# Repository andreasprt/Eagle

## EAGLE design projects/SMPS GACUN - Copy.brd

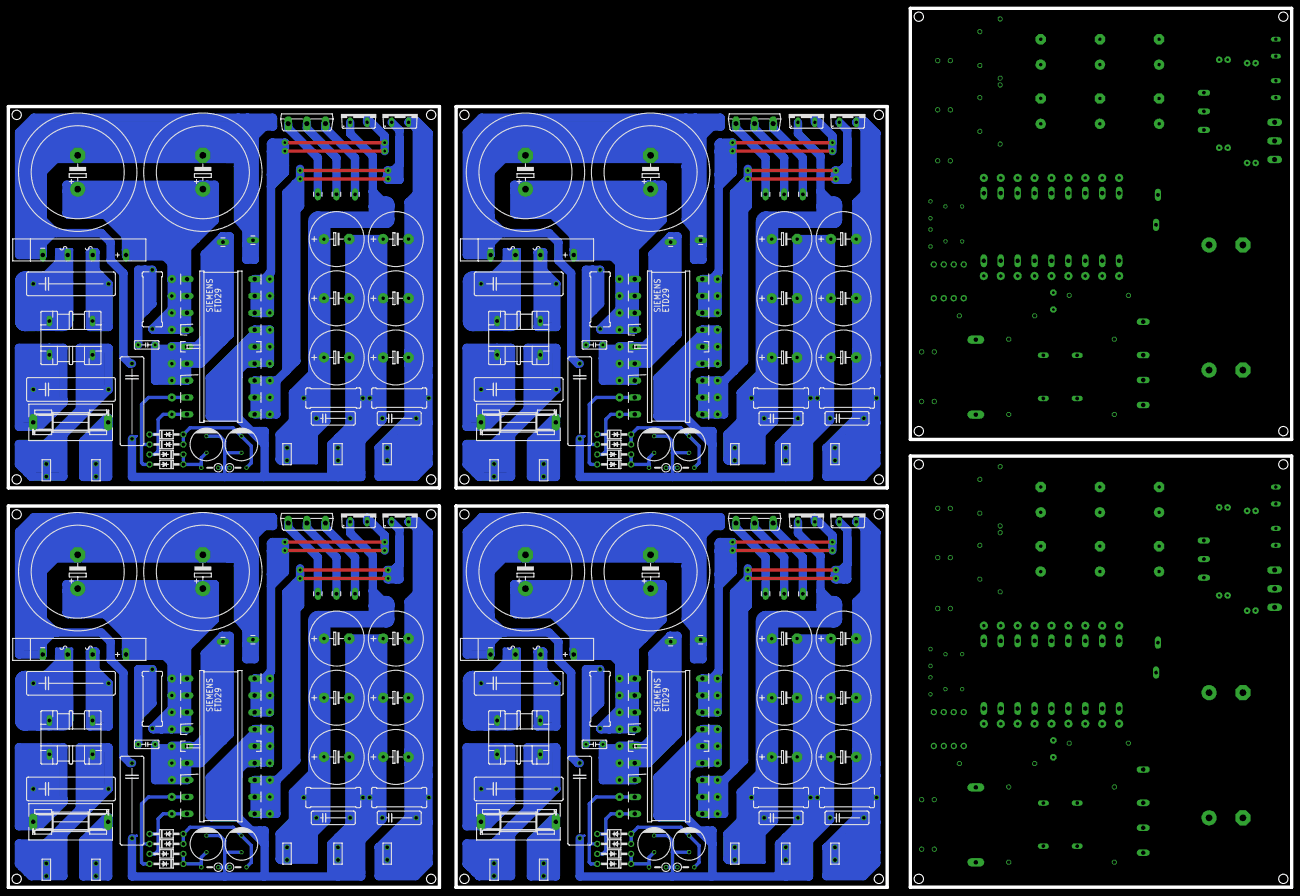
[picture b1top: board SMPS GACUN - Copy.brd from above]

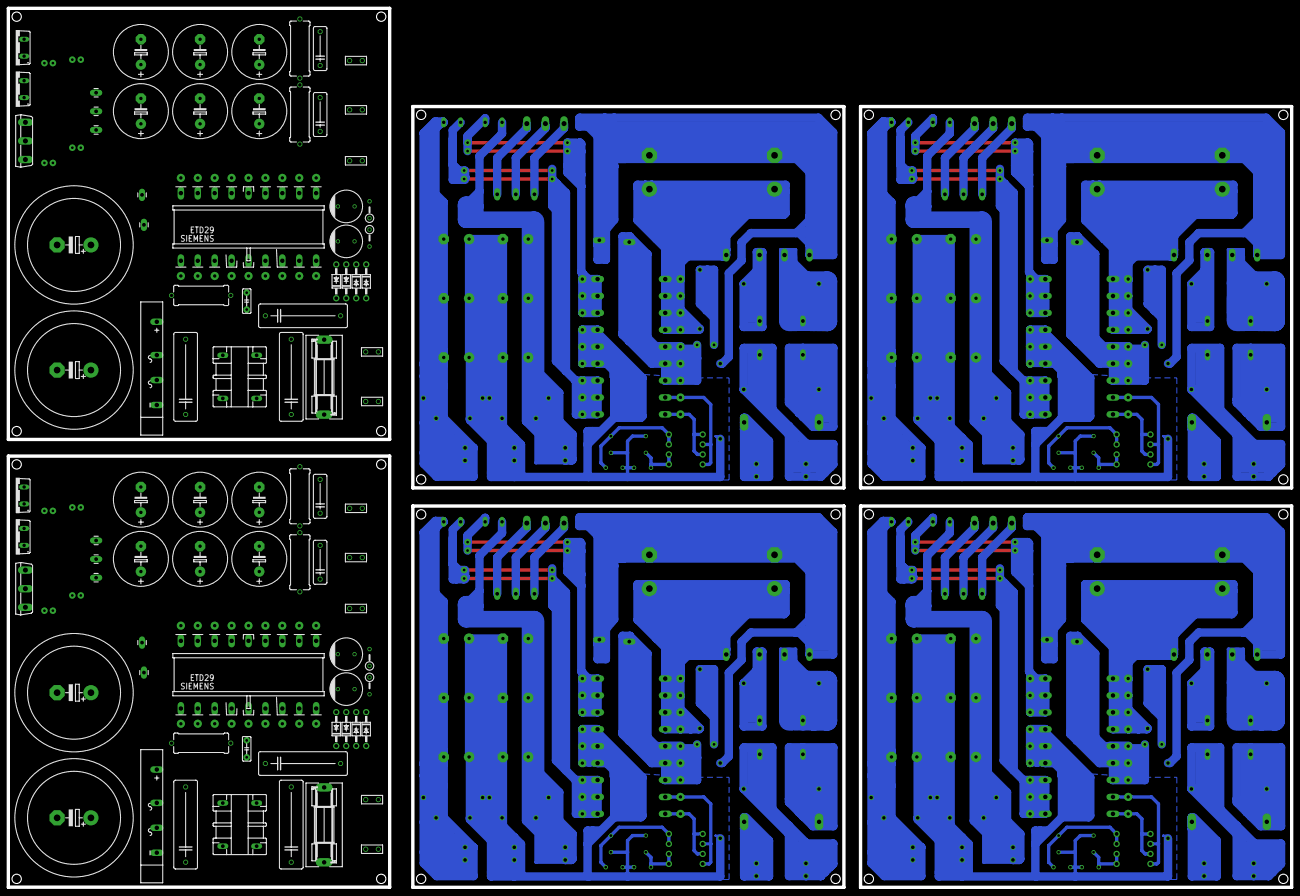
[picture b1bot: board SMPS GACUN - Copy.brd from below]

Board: 2 copper layers, 385.5 x 264.1 mm, 252 parts (84 on the bottom side), 88 nets.

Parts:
B1, B2, B3, B4, B5, B6: RECTIFIER-DSI32; DSI32
C1, C2, C5, C17, C23, C26, C33, C39, C42, C49, C55, C58, C65, C71, C74, C81, C87, C90: C225-074X268
C3, C14, C22, C24, C38, C40, C54, C56, C70, C72, C86, C88: EB35D
C4, C25, C41, C57, C73, C89: C050-025X075
C6, C7, C8, C9, C10, C11, C18, C19, C27, C28, C29, C30, C34, C35, C43, C44, C45, C46, C50, C51, C59, C60, C61, C62, C66, C67, C75, C76, C77, C78, C82, C83, C91, C92, C93, C94: E7,5-16
C12, C13, C20, C21, C36, C37, C52, C53, C68, C69, C84, C85: C102-043X133
C15, C16, C31, C32, C47, C48, C63, C64, C79, C80, C95, C96: SANYO-OSCON_F13
D1, D2, D7, D8, D13, D14, D19, D20, D25, D26, D31, D32: BYT08P; TO220ACS
D3, D4, D5, D6, D9, D10, D11, D12, D15, D16, D17, D18, D21, D22, D23, D24, D27, D28, D29, D30, D33, D34, D35, D36: 1N4004; DO41-10
F1, F2, F3, F4, F5, F6: SH22,5A
J1, J5, J6, J7, J8, J13, J14, J15, J16, J17, J23, J24, J25, J26, J27, J33, J34, J35, J36, J37, J43, J44, J45, J46, J47, J53, J54, J55, J56, J57: 1X01_LONGPAD
J2, J3, J4, J9, J10, J11, J12, J18, J19, J20, J21, J22, J28, J29, J30, J31, J32, J38, J39, J40, J41, J42, J48, J49, J50, J51, J52, J58, J59, J60: 1X02_BIG
L1, L3, L5, L7, L9, L11: MFE
L2, L4, L6, L8, L10, L12: ST-D4
Q1, Q2, Q3, Q4, Q5, Q6: IRFPC40; TO247BV
R1, R2, R3, R6, R7, R8, R11, R12, R13, R16, R17, R18, R21, R22, R23, R26, R27, R28: 0617/17
R4, R5, R9, R10, R14, R15, R19, R20, R24, R25, R29, R30: 0207/5V

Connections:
GND: C5.2, C6.-, C7.+, C8.-, C9.+, C10.-, C11.+, C12.2, C13.1, C15.-, C16.+, J9.P$1, J9.P$2, L2.4, L2.P$4, L2.P$5, R2.2, R3.1, R4.1, R5.1
GND1: C18.-, C19.+, C20.2, C21.1, C26.2, C27.-, C28.+, C29.-, C30.+, C31.-, C32.+, J19.P$1, J19.P$2, L4.4, L4.P$4, L4.P$5, R7.2, R8.1, R9.1, R10.1
GND2: C34.-, C35.+, C36.2, C37.1, C42.2, C43.-, C44.+, C45.-, C46.+, C47.-, C48.+, J29.P$1, J29.P$2, L6.4, L6.P$4, L6.P$5, R12.2, R13.1, R14.1, R15.1
GND3: C50.-, C51.+, C52.2, C53.1, C58.2, C59.-, C60.+, C61.-, C62.+, C63.-, C64.+, J39.P$1, J39.P$2, L8.4, L8.P$4, L8.P$5, R17.2, R18.1, R19.1, R20.1
GND4: C74.2, C79.-, C80.+, R24.1, R25.1
GND5: C90.2, C95.-, C96.+, R29.1, R30.1
unnamed: C1.1, F1.2, L1.4
unnamed: B1.AC2, C2.1, L1.3
unnamed: C1.2, J2.P$1, J2.P$2, L1.1
unnamed: B1.AC1, C2.2, L1.2
unnamed: C4.2, J5.1, L2.1, L2.5, L2.P$1
unnamed: B1.-, C3.-, C5.1, C14.-, J1.1
unnamed: C4.1, R1.2
unnamed: F1.1, J4.P$1, J4.P$2
unnamed: J6.1, Q1.S
unnamed: C6.+, C8.+, C10.+, C12.1, D1.C, J3.P$1, J3.P$2, R2.1
unnamed: J7.1, Q1.G
unnamed: D2.C, L2.2, L2.7, L2.8
unnamed: J8.1, Q1.D
unnamed: B1.+, C3.+, C14.+, L2.11, L2.13, L2.P$2, L2.P$3, R1.1
unnamed: C7.-, C9.-, C11.-, C13.2, D2.A, J10.P$1, J10.P$2, R3.2
unnamed: D1.A, L2.10, L2.12, L2.14
unnamed: D5.A, D6.C, L2.3
unnamed: C17.1, F2.2, L3.4
unnamed: B2.AC2, C23.1, L3.3
unnamed: C15.+, D4.C, D5.C, R4.2
unnamed: C16.-, D3.A, D6.A, R5.2
unnamed: D3.C, D4.A, L2.6
unnamed: C17.2, J11.P$1, J11.P$2, L3.1
unnamed: B2.AC1, C23.2, L3.2
unnamed: C25.2, J14.1, L4.1, L4.5, L4.P$1
unnamed: B2.-, C22.-, C24.-, C26.1, J13.1
unnamed: C25.1, R6.2
unnamed: C18.+, C20.1, C27.+, C29.+, D7.C, J18.P$1, J18.P$2, R7.1
unnamed: D8.C, L4.2, L4.7, L4.8
unnamed: D7.A, L4.10, L4.12, L4.14
unnamed: F2.1, J12.P$1, J12.P$2
unnamed: B2.+, C22.+, C24.+, L4.11, L4.13, L4.P$2, L4.P$3, R6.1
unnamed: J15.1, Q2.S
unnamed: J16.1, Q2.G
unnamed: J17.1, Q2.D
unnamed: C19.-, C21.2, C28.-, C30.-, D8.A, J20.P$1, J20.P$2, R8.2
unnamed: D11.A, D12.C, L4.3
unnamed: C31.+, D10.C, D11.C, R9.2
unnamed: C32.-, D9.A, D12.A, R10.2
unnamed: D9.C, D10.A, L4.6
unnamed: C33.1, F3.2, L5.4
unnamed: B3.AC2, C39.1, L5.3
unnamed: C33.2, J21.P$1, J21.P$2, L5.1
unnamed: B3.AC1, C39.2, L5.2
unnamed: C41.2, J24.1, L6.1, L6.5, L6.P$1
unnamed: B3.-, C38.-, C40.-, C42.1, J23.1
unnamed: C41.1, R11.2
unnamed: C34.+, C36.1, C43.+, C45.+, D13.C, J28.P$1, J28.P$2, R12.1
unnamed: D14.C, L6.2, L6.7, L6.8
unnamed: D13.A, L6.10, L6.12, L6.14
unnamed: F3.1, J22.P$1, J22.P$2
unnamed: B3.+, C38.+, C40.+, L6.11, L6.13, L6.P$2, L6.P$3, R11.1
unnamed: J25.1, Q3.S
unnamed: J26.1, Q3.G
unnamed: J27.1, Q3.D
unnamed: C35.-, C37.2, C44.-, C46.-, D14.A, J30.P$1, J30.P$2, R13.2
unnamed: D17.A, D18.C, L6.3
unnamed: C47.+, D16.C, D17.C, R14.2
unnamed: C48.-, D15.A, D18.A, R15.2
unnamed: D15.C, D16.A, L6.6
unnamed: C49.1, F4.2, L7.4
unnamed: B4.AC2, C55.1, L7.3
unnamed: C49.2, J31.P$1, J31.P$2, L7.1
unnamed: B4.AC1, C55.2, L7.2
unnamed: C57.2, J34.1, L8.1, L8.5, L8.P$1
unnamed: B4.-, C54.-, C56.-, C58.1, J33.1
unnamed: C57.1, R16.2
unnamed: C50.+, C52.1, C59.+, C61.+, D19.C, J38.P$1, J38.P$2, R17.1
unnamed: D20.C, L8.2, L8.7, L8.8
unnamed: D19.A, L8.10, L8.12, L8.14
unnamed: F4.1, J32.P$1, J32.P$2
unnamed: B4.+, C54.+, C56.+, L8.11, L8.13, L8.P$2, L8.P$3, R16.1
unnamed: J35.1, Q4.S
unnamed: J36.1, Q4.G
unnamed: J37.1, Q4.D
unnamed: C51.-, C53.2, C60.-, C62.-, D20.A, J40.P$1, J40.P$2, R18.2
unnamed: D23.A, D24.C, L8.3
unnamed: C63.+, D22.C, D23.C, R19.2
unnamed: C64.-, D21.A, D24.A, R20.2
unnamed: D21.C, D22.A, L8.6
S$67: C69.2, R23.2
S$153: C85.2, R28.2

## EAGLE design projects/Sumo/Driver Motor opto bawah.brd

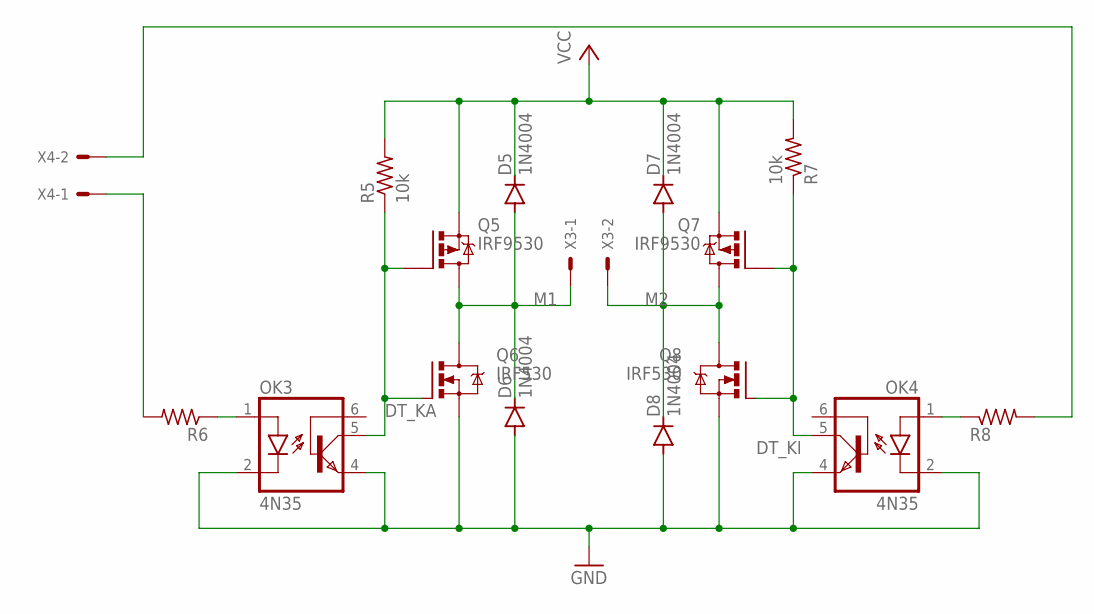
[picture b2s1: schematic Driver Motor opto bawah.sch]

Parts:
D5, D6, D7, D8: 1N4004; DO41-10
OK3, OK4: 4N35; DIL06
Q5, Q7: IRF9530; TO220BV
Q6, Q8: IRF530; TO220BV
R5, R7: 10k; 0207/10
R6, R8: R-US_0207/10; 0207/10
X3, X4: 22-23-2021

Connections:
DT_KA: OK3.5 (COL), Q5.G, Q6.G, R5.1
DT_KI: OK4.5 (COL), Q7.G, Q8.G, R7.1
GND: D6.A, D8.A, OK3.2 (C), OK3.4 (EMI), OK4.2 (C), OK4.4 (EMI), Q6.S, Q8.S
M1: D5.A, D6.C, Q5.D, Q6.D, X3.1
M2: D7.A, D8.C, Q7.D, Q8.D, X3.2
unnamed: OK4.1 (A), R8.1
unnamed: OK3.1 (A), R6.1
unnamed: R6.2, X4.1
unnamed: R8.2, X4.2
VCC: D5.C, D7.C, Q5.S, Q7.S, R5.2, R7.2

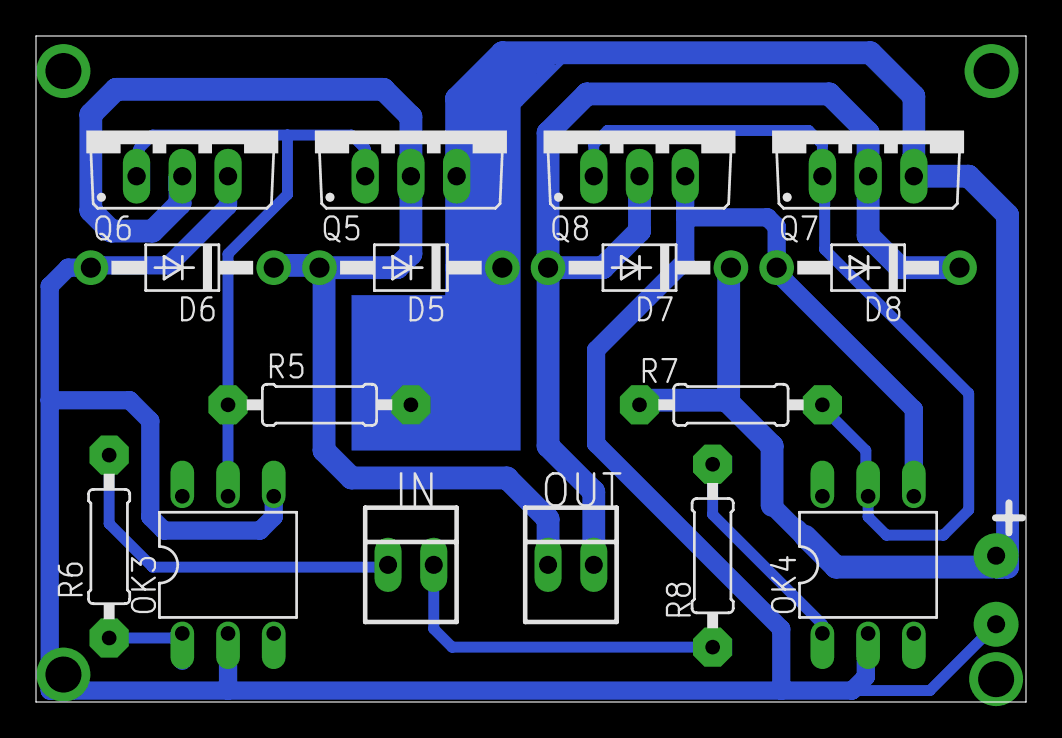
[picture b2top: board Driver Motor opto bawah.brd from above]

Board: 2 copper layers, 55.0 x 37.0 mm, 16 parts (0 on the bottom side), 10 nets.

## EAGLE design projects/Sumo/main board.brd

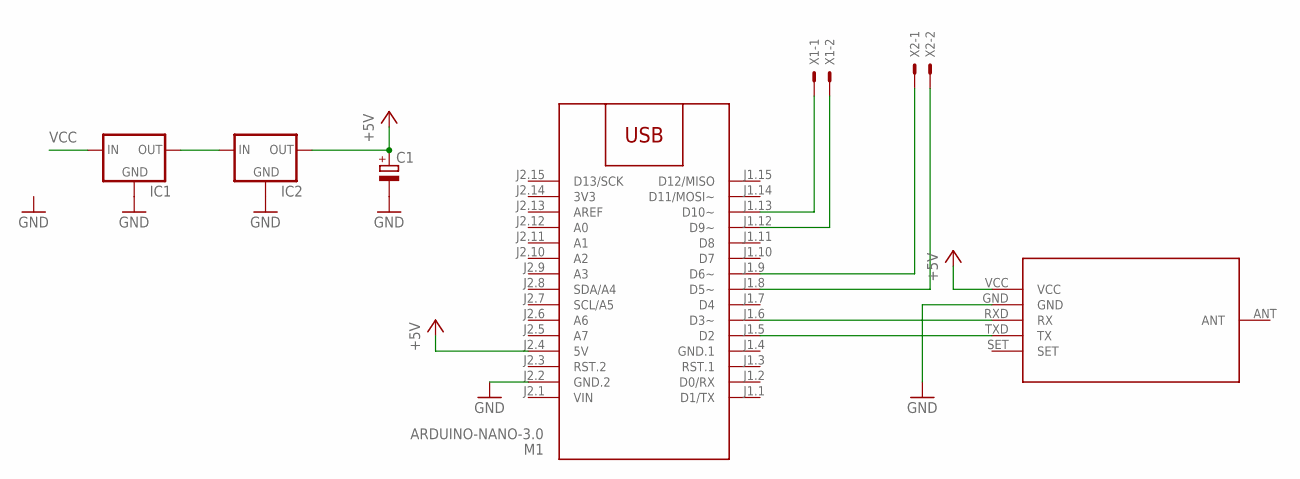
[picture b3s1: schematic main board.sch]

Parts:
C1: CPOL-EUE2.5-7; E2,5-7
IC1, IC2: 78XXS
M1: ARDUINO-NANO-3.0
U$1: HC-12_FOOTPRINT
X1, X2: 22-23-2021

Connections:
3V3: M1.J2.14 (3V3)
+5V: C1.+, IC2.OUT, M1.J2.4 (5V), U$1.VCC
GND: C1.-, IC1.GND, IC2.GND, M1.J2.2 (GND.2), U$1.GND
GND.1: M1.J1.4 (GND.1)
unnamed: M1.J1.5 (D2), U$1.TXD (TX)
unnamed: M1.J1.6 (D3~), U$1.RXD (RX)
unnamed: M1.J1.13 (D10~), X1.1
unnamed: M1.J1.12 (D9~), X1.2
unnamed: M1.J1.9 (D6~), X2.1
unnamed: M1.J1.8 (D5~), X2.2
unnamed: IC1.OUT, IC2.IN
VCC: IC1.IN
VIN: M1.J2.1 (VIN)

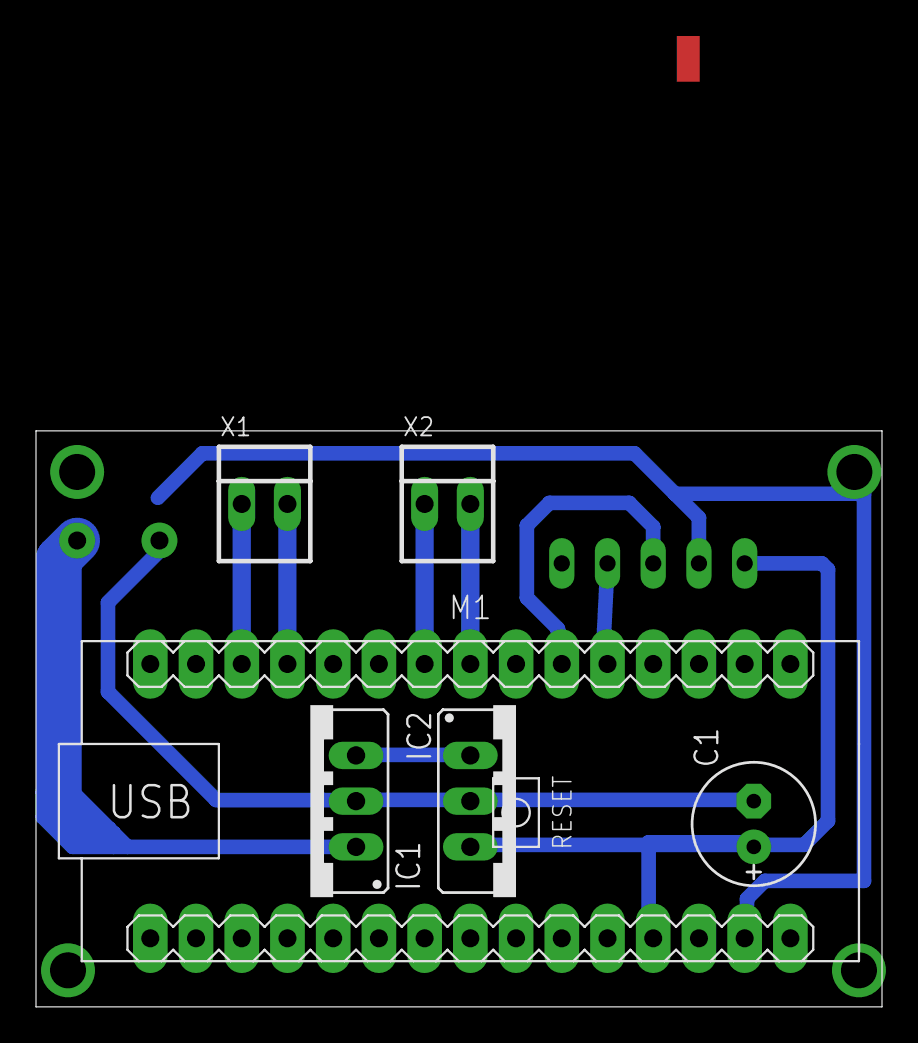
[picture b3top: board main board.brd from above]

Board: 2 copper layers, 47.0 x 32.0 mm, 7 parts (0 on the bottom side), 9 nets.

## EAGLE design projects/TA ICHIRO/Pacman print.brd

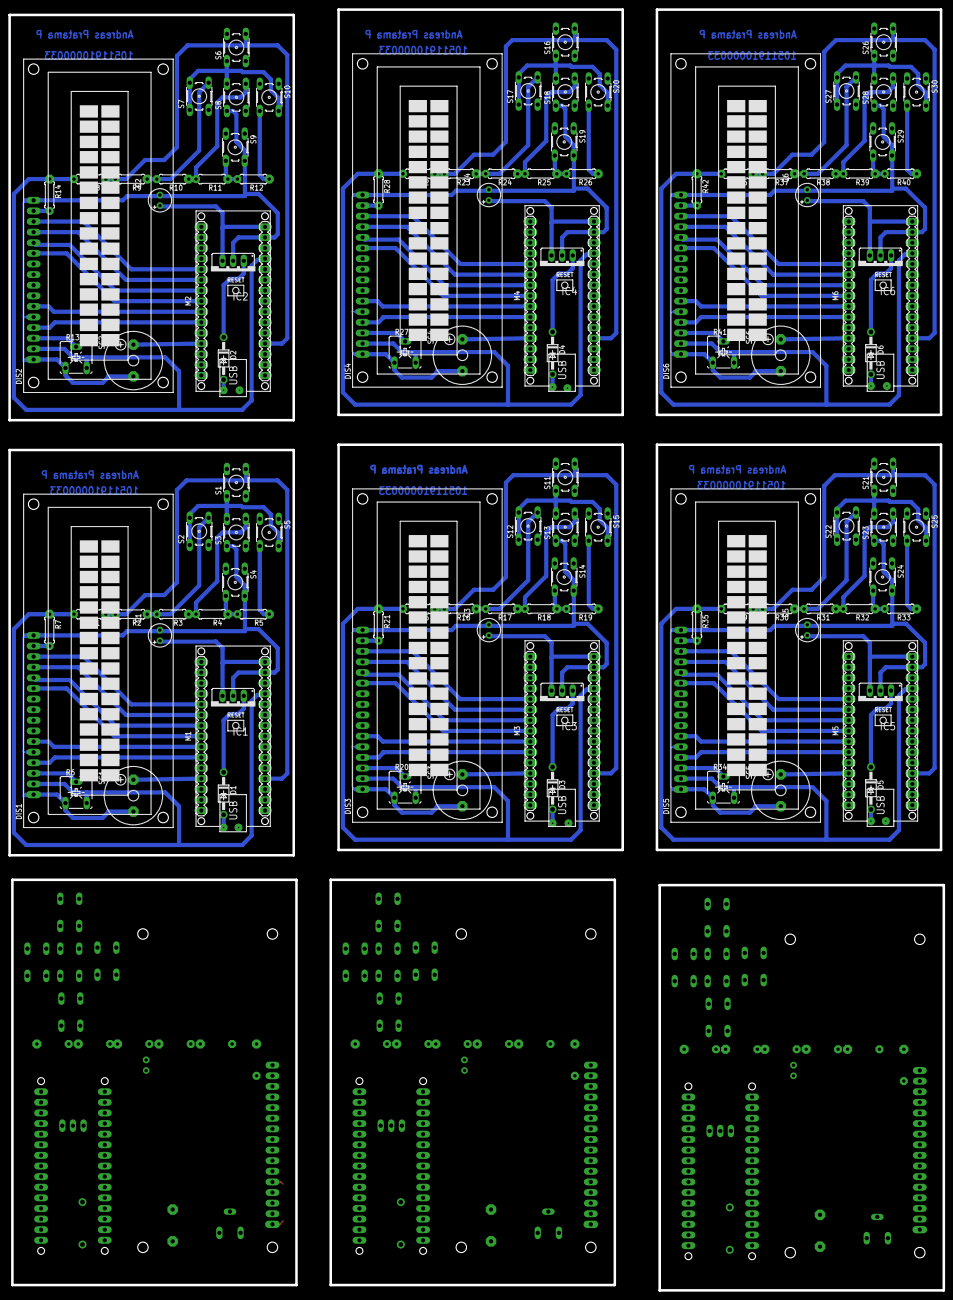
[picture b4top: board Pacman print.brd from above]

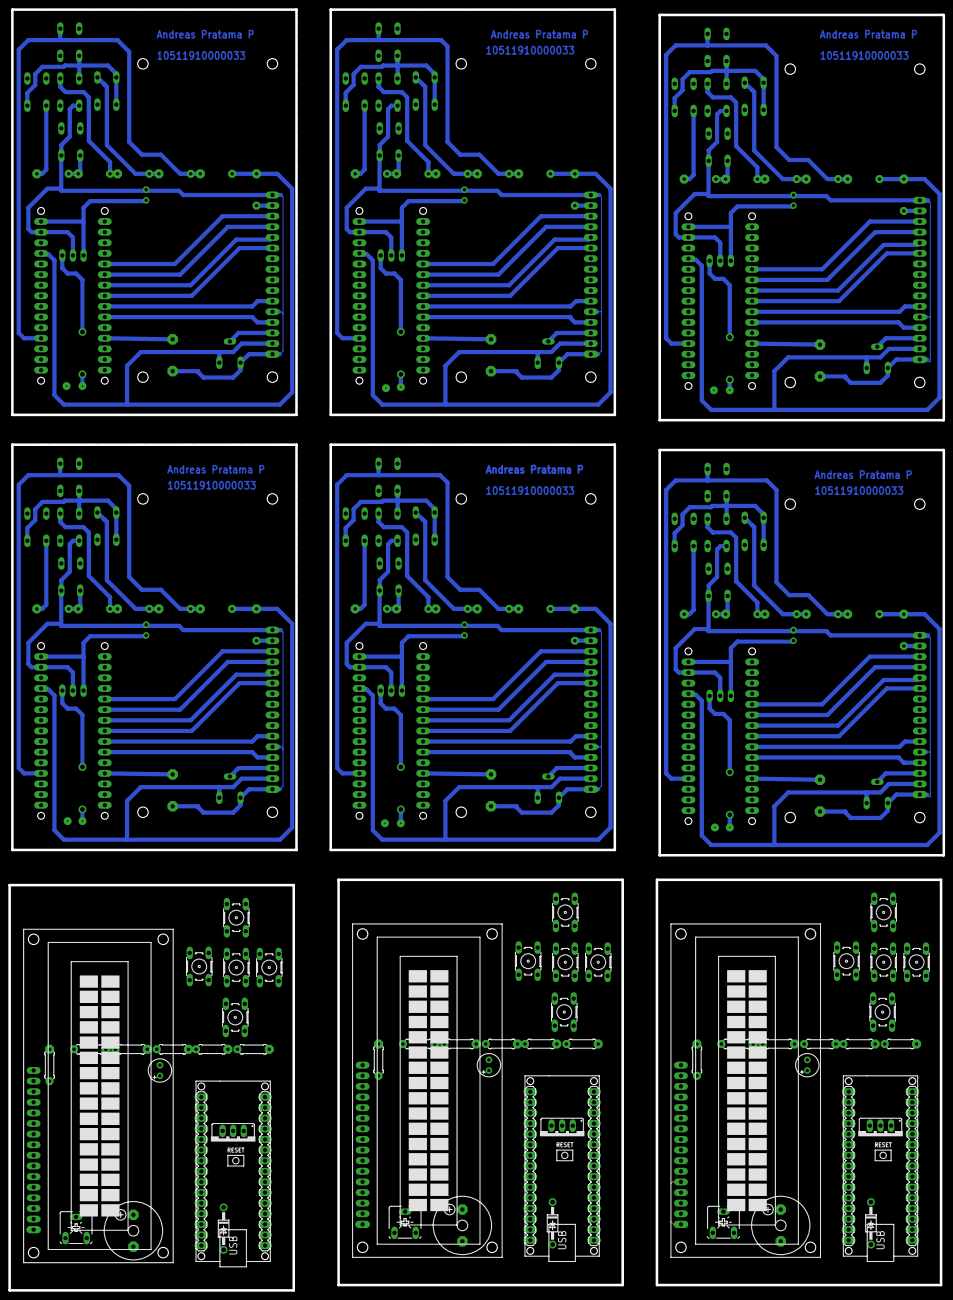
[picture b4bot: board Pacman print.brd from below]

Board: 2 copper layers, 223.6 x 306.6 mm, 162 parts (54 on the bottom side), 103 nets.

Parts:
C1, C2, C3, C4, C5, C6, C7, C8, C9: E2,5-6
D1, D2, D3, D4, D5, D6, D7, D8, D9: 1N4004; DO41-10
DIS1, DIS2, DIS3, DIS4, DIS5, DIS6, DIS7, DIS8, DIS9: TUXGR_16X2_R2
IC1, IC2, IC3, IC4, IC5, IC6, IC7, IC8, IC9: 78XXS
M1, M2, M3, M4, M5, M6, M7, M8, M9: ARDUINO-NANO-3.0
R1, R2, R3, R4, R5, R7, R8, R9, R10, R11, R12, R14, R15, R16, R17, R18, R19, R21, R22, R23, R24, R25, R26, R28, R29, R30, R31, R32, R33, R35, R36, R37, R38, R39, R40, R42, R43, R44, R45, R46, R47, R49, R50, R51, R52, R53, R54, R56, R57, R58, R59, R60, R61, R63: 0207/7
R6, R13, R20, R27, R34, R41, R48, R55, R62: CA6V
S1, S2, S3, S4, S5, S6, S7, S8, S9, S10, S11, S12, S13, S14, S15, S16, S17, S18, S19, S20, S21, S22, S23, S24, S25, S26, S27, S28, S29, S30, S31, S32, S33, S34, S35, S36, S37, S38, S39, S40, S41, S42, S43, S44, S45: B3F-10XX
SG1, SG2, SG3, SG4, SG5, SG6, SG7, SG8, SG9: F/CM12P

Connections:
1: DIS2.14, M2.J1.5
2: DIS1.14, M1.J1.5
3: DIS1.13, M1.J1.6
4: DIS1.11, M1.J1.8
5: DIS1.12, M1.J1.7
5V1: DIS2.2, M2.J2.4, R8.2, R13.E, R14.1
5V2: DIS1.2, M1.J2.4, R1.2, R6.E, R7.1
5V3: DIS4.2, M4.J2.4, R22.2, R27.E, R28.1
5V4: DIS3.2, M3.J2.4, R15.2, R20.E, R21.1
5V5: DIS6.2, M6.J2.4, R36.2, R41.E, R42.1
5V6: DIS5.2, M5.J2.4, R29.2, R34.E, R35.1
6: DIS1.6, M1.J1.9
8: DIS2.13, M2.J1.6
9: DIS1.4, M1.J1.10
10: DIS2.11, M2.J1.8
11: DIS2.12, M2.J1.7
12: DIS2.6, M2.J1.9
13: DIS2.4, M2.J1.10
14: M2.J1.12, SG2.+
15: M1.J1.12, SG1.+
16: DIS3.14, M3.J1.5
17: DIS3.13, M3.J1.6
18: DIS3.11, M3.J1.8
19: DIS3.12, M3.J1.7
20: DIS3.6, M3.J1.9
21: DIS3.4, M3.J1.10
22: DIS4.14, M4.J1.5
23: DIS4.13, M4.J1.6
24: DIS4.11, M4.J1.8
25: DIS4.12, M4.J1.7
26: DIS4.6, M4.J1.9
27: DIS4.4, M4.J1.10
28: M4.J1.12, SG4.+
29: M3.J1.12, SG3.+
30: DIS5.14, M5.J1.5
31: DIS5.13, M5.J1.6
32: DIS5.11, M5.J1.8
33: DIS5.12, M5.J1.7
35: DIS5.6, M5.J1.9
36: DIS6.14, M6.J1.5
37: DIS6.13, M6.J1.6
38: DIS6.11, M6.J1.8
39: DIS6.12, M6.J1.7
40: DIS6.6, M6.J1.9
41: DIS6.4, M6.J1.10
42: M6.J1.12, SG6.+
43: DIS5.4, M5.J1.10
44: M5.J1.12, SG5.+
+5V1: C2.+, IC2.OUT, M2.J2.1
+5V2: C1.+, IC1.OUT, M1.J2.1
+5V3: C4.+, IC4.OUT, M4.J2.1
+5V4: C3.+, IC3.OUT, M3.J2.1
+5V5: C6.+, IC6.OUT, M6.J2.1
+5V6: C5.+, IC5.OUT, M5.J2.1
A1: M2.J2.12, R8.1, R9.2, S6.4
A2: M1.J2.12, R1.1, R2.2, S1.4
A3: M4.J2.12, R22.1, R23.2, S16.4
A4: M3.J2.12, R15.1, R16.2, S11.4
A5: M6.J2.12, R36.1, R37.2, S26.4
A6: M5.J2.12, R29.1, R30.2, S21.4
CN1: DIS2.3, R13.S
CN2: DIS1.3, R6.S
CN3: DIS4.3, R27.S
CN4: DIS3.3, R20.S
CN5: DIS6.3, R41.S
CN6: DIS5.3, R34.S
GND2: C1.-, C2.-, C3.-, C4.-, C5.-, C6.-, DIS1.1, DIS1.5, DIS1.16, DIS2.1, DIS2.5, DIS2.16, DIS3.1, DIS3.5, DIS3.16, DIS4.1, DIS4.5, DIS4.16, DIS5.1, DIS5.5, DIS5.16, DIS6.1, DIS6.5, DIS6.16, IC1.GND, IC2.GND, IC3.GND, IC4.GND, IC5.GND, IC6.GND, M1.J2.2, M2.J2.2, M3.J2.2, M4.J2.2, M5.J2.2, M6.J2.2, R6.A, R13.A, R20.A, R27.A, R34.A, R41.A, S1.1, S1.2, S2.1, S2.2, S3.1, S3.2, S4.2, S5.2, S6.1, S6.2, S7.1, S7.2, S8.1, S8.2, S9.2, S10.2, S11.1, S11.2, S12.1, S12.2, S13.1, S13.2, S14.2, S15.2, S16.1, S16.2, S17.1, S17.2, S18.1, S18.2, S19.2, S20.2, S21.1, S21.2, S22.1, S22.2, S23.1, S23.2, S24.2, S25.2, S26.1, S26.2, S27.1, S27.2, S28.1, S28.2, S29.2, S30.2, SG1.-, SG2.-, SG3.-, SG4.-, SG5.-, SG6.-
unnamed: D1.C, IC1.IN
unnamed: R2.1, R3.2, S2.4
unnamed: R3.1, R4.2, S3.4
unnamed: R4.1, R5.2, S4.4
unnamed: R5.1, S5.4
unnamed: D2.C, IC2.IN
unnamed: R9.1, R10.2, S7.4
unnamed: R10.1, R11.2, S8.4
unnamed: R11.1, R12.2, S9.4
unnamed: R12.1, S10.4
unnamed: DIS2.15, R14.2
unnamed: DIS1.15, R7.2
unnamed: D3.C, IC3.IN
unnamed: R16.1, R17.2, S12.4
unnamed: R17.1, R18.2, S13.4
unnamed: D4.C, IC4.IN
unnamed: R23.1, R24.2, S17.4
unnamed: R24.1, R25.2, S18.4
unnamed: R25.1, R26.2, S19.4
unnamed: R26.1, S20.4
unnamed: DIS4.15, R28.2
unnamed: R18.1, R19.2, S14.4
unnamed: R19.1, S15.4
unnamed: DIS3.15, R21.2
unnamed: D5.C, IC5.IN
unnamed: R30.1, R31.2, S22.4
unnamed: D6.C, IC6.IN
unnamed: R37.1, R38.2, S27.4
unnamed: R38.1, R39.2, S28.4
unnamed: R39.1, R40.2, S29.4
unnamed: R40.1, S30.4
unnamed: DIS6.15, R42.2
unnamed: R31.1, R32.2, S23.4
unnamed: R32.1, R33.2, S24.4
unnamed: R33.1, S25.4
unnamed: DIS5.15, R35.2

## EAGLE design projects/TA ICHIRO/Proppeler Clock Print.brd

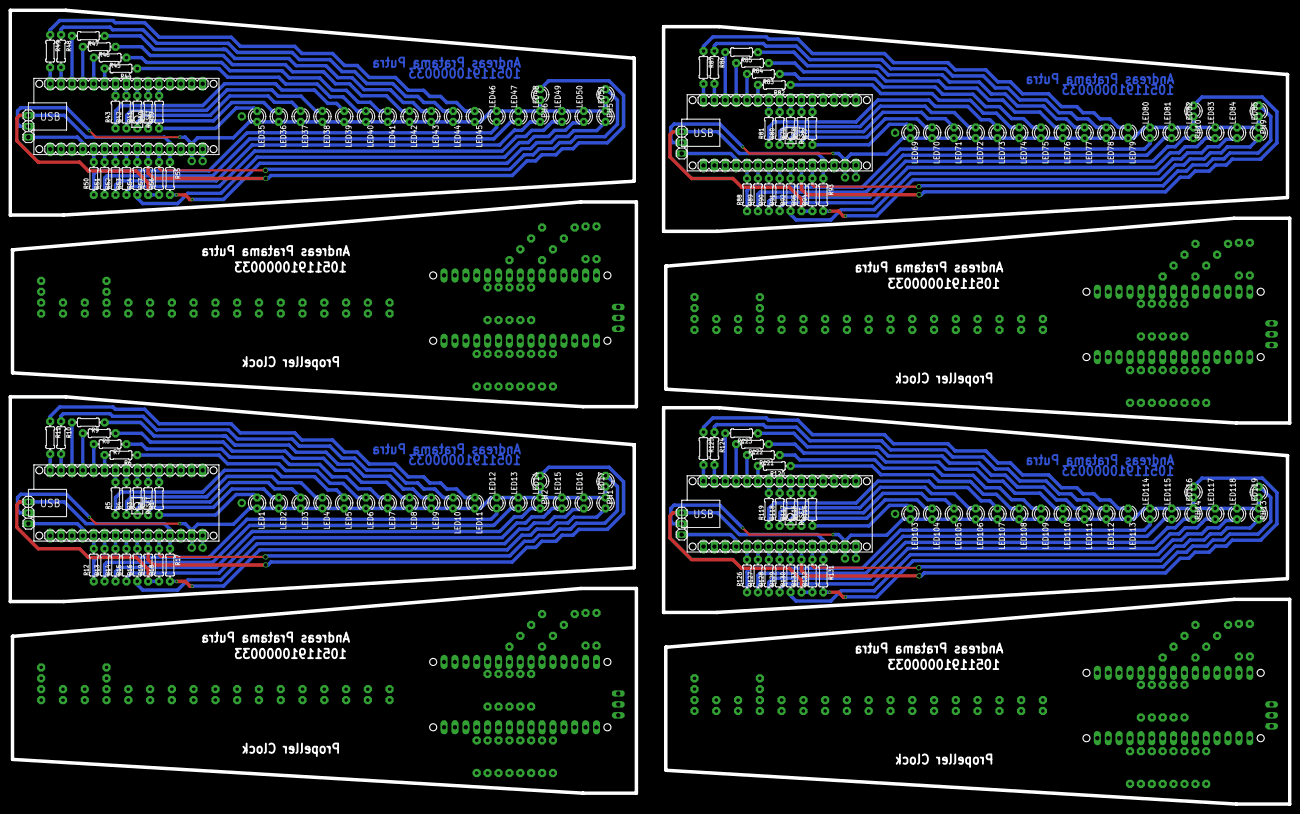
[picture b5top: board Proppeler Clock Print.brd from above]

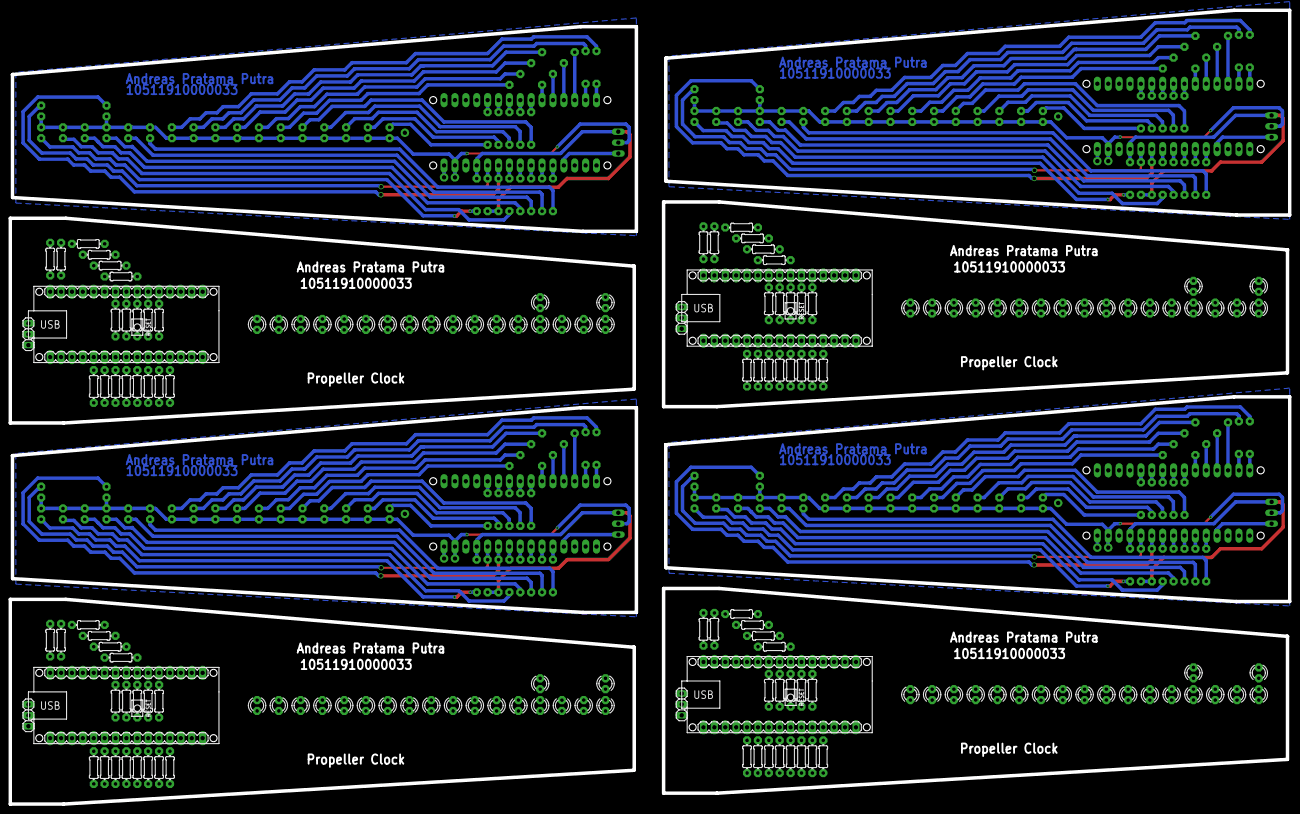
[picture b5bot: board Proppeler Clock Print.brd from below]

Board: 2 copper layers, 298.4 x 185.2 mm, 320 parts (160 on the bottom side), 160 nets.

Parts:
JP1, JP2, JP3, JP4, JP5, JP6, JP7, JP8: 1X03
LED1, LED2, LED3, LED4, LED5, LED6, LED7, LED8, LED9, LED10, LED11, LED12, LED13, LED14, LED15, LED16, LED17, LED18, LED19, LED20, LED21, LED22, LED23, LED24, LED25, LED26, LED27, LED28, LED29, LED30, LED31, LED32, LED33, LED34, LED35, LED36, LED37, LED38, LED39, LED40, LED41, LED42, LED43, LED44, LED45, LED46, LED47, LED48, LED49, LED50, LED51, LED52, LED53, LED54, LED55, LED56, LED57, LED58, LED59, LED60, LED61, LED62, LED63, LED64, LED65, LED66, LED67, LED68, LED69, LED70, LED71, LED72, LED73, LED74, LED75, LED76, LED77, LED78, LED79, LED80, LED81, LED82, LED83, LED84, LED85, LED86, LED87, LED88, LED89, LED90, LED91, LED92, LED93, LED94, LED95, LED96, LED97, LED98, LED99, LED100, LED101, LED102, LED103, LED104, LED105, LED106, LED107, LED108, LED109, LED110, LED111, LED112, LED113, LED114, LED115, LED116, LED117, LED118, LED119, LED120, LED121, LED122, LED123, LED124, LED125, LED126, LED127, LED128, LED129, LED130, LED131, LED132, LED133, LED134, LED135, LED136: LED3MM
M1, M2, M3, M4, M5, M6, M7, M8: ARDUINO-NANO-3.0
PH1, PH2, PH3, PH4, PH5, PH6, PH7, PH8, PH9, PH10, PH11, PH12, PH13, PH14, PH15, PH16: LED3MM
R1, R20, R39, R58, R77, R96, R115, R134: 330; 0204/7
R2, R3, R4, R5, R6, R7, R8, R9, R10, R11, R12, R13, R14, R15, R16, R21, R22, R23, R24, R25, R26, R27, R28, R29, R30, R31, R32, R33, R34, R35, R40, R41, R42, R43, R44, R45, R46, R47, R48, R49, R50, R51, R52, R53, R54, R59, R60, R61, R62, R63, R64, R65, R66, R67, R68, R69, R70, R71, R72, R73, R78, R79, R80, R81, R82, R83, R84, R85, R86, R87, R88, R89, R90, R91, R92, R97, R98, R99, R100, R101, R102, R103, R104, R105, R106, R107, R108, R109, R110, R111, R116, R117, R118, R119, R120, R121, R122, R123, R124, R125, R126, R127, R128, R129, R130, R135, R136, R137, R138, R139, R140, R141, R142, R143, R144, R145, R146, R147, R148, R149: 0204/7
R17, R36, R55, R74, R93, R112, R131, R150: 2k2; 0204/7
R18, R19, R37, R38, R56, R57, R75, R76, R94, R95, R113, R114, R132, R133, R151, R152: 10k; 0204/7

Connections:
2: M1.J1.5, M2.J1.5, M3.J1.5, M4.J1.5, M5.J1.5, M6.J1.5, M7.J1.5, M8.J1.5, R1.2, R20.2, R39.2, R58.2, R77.2, R96.2, R115.2, R134.2
3: M1.J1.6, M2.J1.6, M3.J1.6, M4.J1.6, M5.J1.6, M6.J1.6, M7.J1.6, M8.J1.6, R2.2, R21.2, R40.2, R59.2, R78.2, R97.2, R116.2, R135.2
3V3: M1.J2.14, M2.J2.14, M3.J2.14, M4.J2.14, M5.J2.14, M6.J2.14, M7.J2.14, M8.J2.14
4: M1.J1.7, M2.J1.7, M3.J1.7, M4.J1.7, M5.J1.7, M6.J1.7, M7.J1.7, M8.J1.7, R3.2, R22.2, R41.2, R60.2, R79.2, R98.2, R117.2, R136.2
5: M1.J1.8, M2.J1.8, M3.J1.8, M4.J1.8, M5.J1.8, M6.J1.8, M7.J1.8, M8.J1.8, R4.2, R23.2, R42.2, R61.2, R80.2, R99.2, R118.2, R137.2
5V: JP1.1, JP2.1, JP3.1, JP4.1, JP5.1, JP6.1, JP7.1, JP8.1, M1.J2.4, M2.J2.4, M3.J2.4, M4.J2.4, M5.J2.4, M6.J2.4, M7.J2.4, M8.J2.4, R17.1, R18.1, R19.1, R36.1, R37.1, R38.1, R55.1, R56.1, R57.1, R74.1, R75.1, R76.1, R93.1, R94.1, R95.1, R112.1, R113.1, R114.1, R131.1, R132.1, R133.1, R150.1, R151.1, R152.1
6: M1.J1.9, M2.J1.9, M3.J1.9, M4.J1.9, M5.J1.9, M6.J1.9, M7.J1.9, M8.J1.9, R5.2, R24.2, R43.2, R62.2, R81.2, R100.2, R119.2, R138.2
7: M1.J1.10, M2.J1.10, M3.J1.10, M4.J1.10, M5.J1.10, M6.J1.10, M7.J1.10, M8.J1.10, R6.2, R25.2, R44.2, R63.2, R82.2, R101.2, R120.2, R139.2
8: M1.J1.11, M2.J1.11, M3.J1.11, M4.J1.11, M5.J1.11, M6.J1.11, M7.J1.11, M8.J1.11, R7.2, R26.2, R45.2, R64.2, R83.2, R102.2, R121.2, R140.2
9: M1.J1.12, M2.J1.12, M3.J1.12, M4.J1.12, M5.J1.12, M6.J1.12, M7.J1.12, M8.J1.12, R8.2, R27.2, R46.2, R65.2, R84.2, R103.2, R122.2, R141.2
10: M1.J1.13, M2.J1.13, M3.J1.13, M4.J1.13, M5.J1.13, M6.J1.13, M7.J1.13, M8.J1.13, R9.2, R28.2, R47.2, R66.2, R85.2, R104.2, R123.2, R142.2
11: M1.J1.14, M2.J1.14, M3.J1.14, M4.J1.14, M5.J1.14, M6.J1.14, M7.J1.14, M8.J1.14, R10.2, R29.2, R48.2, R67.2, R86.2, R105.2, R124.2, R143.2
12: M1.J1.15, M2.J1.15, M3.J1.15, M4.J1.15, M5.J1.15, M6.J1.15, M7.J1.15, M8.J1.15, R11.2, R30.2, R49.2, R68.2, R87.2, R106.2, R125.2, R144.2
A0: JP1.3, JP2.3, JP3.3, JP4.3, JP5.3, JP6.3, JP7.3, JP8.3, M1.J2.12, M2.J2.12, M3.J2.12, M4.J2.12, M5.J2.12, M6.J2.12, M7.J2.12, M8.J2.12
A1: M1.J2.11, M2.J2.11, M3.J2.11, M4.J2.11, M5.J2.11, M6.J2.11, M7.J2.11, M8.J2.11, R12.2, R31.2, R50.2, R69.2, R88.2, R107.2, R126.2, R145.2
A2: M1.J2.10, M2.J2.10, M3.J2.10, M4.J2.10, M5.J2.10, M6.J2.10, M7.J2.10, M8.J2.10, R13.2, R32.2, R51.2, R70.2, R89.2, R108.2, R127.2, R146.2
A3: M1.J2.9, M2.J2.9, M3.J2.9, M4.J2.9, M5.J2.9, M6.J2.9, M7.J2.9, M8.J2.9, R14.2, R33.2, R52.2, R71.2, R90.2, R109.2, R128.2, R147.2
A4: M1.J2.8, M2.J2.8, M3.J2.8, M4.J2.8, M5.J2.8, M6.J2.8, M7.J2.8, M8.J2.8, R15.2, R34.2, R53.2, R72.2, R91.2, R110.2, R129.2, R148.2
A5: M1.J2.7, M2.J2.7, M3.J2.7, M4.J2.7, M5.J2.7, M6.J2.7, M7.J2.7, M8.J2.7, R16.2, R35.2, R54.2, R73.2, R92.2, R111.2, R130.2, R149.2
A6: M1.J2.6, M2.J2.6, M3.J2.6, M4.J2.6, M5.J2.6, M6.J2.6, M7.J2.6, M8.J2.6, PH2.A, PH4.A, PH6.A, PH8.A, PH10.A, PH12.A, PH14.A, PH16.A, R19.2, R38.2, R57.2, R76.2, R95.2, R114.2, R133.2, R152.2
A7: M1.J2.5, M2.J2.5, M3.J2.5, M4.J2.5, M5.J2.5, M6.J2.5, M7.J2.5, M8.J2.5, PH1.A, PH3.A, PH5.A, PH7.A, PH9.A, PH11.A, PH13.A, PH15.A, R18.2, R37.2, R56.2, R75.2, R94.2, R113.2, R132.2, R151.2
GND: JP1.2, JP2.2, JP3.2, JP4.2, JP5.2, JP6.2, JP7.2, JP8.2, LED1.K, LED2.K, LED3.K, LED4.K, LED5.K, LED6.K, LED7.K, LED8.K, LED9.K, LED10.K, LED11.K, LED12.K, LED13.K, LED14.K, LED15.K, LED16.K, LED17.K, LED18.K, LED19.K, LED20.K, LED21.K, LED22.K, LED23.K, LED24.K, LED25.K, LED26.K, LED27.K, LED28.K, LED29.K, LED30.K, LED31.K, LED32.K, LED33.K, LED34.K, LED35.K, LED36.K, LED37.K, LED38.K, LED39.K, LED40.K, LED41.K, LED42.K, LED43.K, LED44.K, LED45.K, LED46.K, LED47.K, LED48.K, LED49.K, LED50.K, LED51.K, LED52.K, LED53.K, LED54.K, LED55.K, LED56.K, LED57.K, LED58.K, LED59.K, LED60.K, LED61.K, LED62.K, LED63.K, LED64.K, LED65.K, LED66.K, LED67.K, LED68.K, LED69.K, LED70.K, LED71.K, LED72.K, LED73.K, LED74.K, LED75.K, LED76.K, LED77.K, LED78.K, LED79.K, LED80.K, LED81.K, LED82.K, LED83.K, LED84.K, LED85.K, LED86.K, LED87.K, LED88.K, LED89.K, LED90.K, LED91.K, LED92.K, LED93.K, LED94.K, LED95.K, LED96.K, LED97.K, LED98.K, LED99.K, LED100.K, LED101.K, LED102.K, LED103.K, LED104.K, LED105.K, LED106.K, LED107.K, LED108.K, LED109.K, LED110.K, LED111.K, LED112.K, LED113.K, LED114.K, LED115.K, LED116.K, LED117.K, LED118.K, LED119.K, LED120.K, LED121.K, LED122.K, LED123.K, LED124.K, LED125.K, LED126.K, LED127.K, LED128.K, LED129.K, LED130.K, LED131.K, LED132.K, LED133.K, LED134.K, LED135.K, LED136.K, M1.J2.2, M2.J2.2, M3.J2.2, M4.J2.2, M5.J2.2, M6.J2.2, M7.J2.2, M8.J2.2, PH1.K, PH2.K, PH3.K, PH4.K, PH5.K, PH6.K, PH7.K, PH8.K, PH9.K, PH10.K, PH11.K, PH12.K, PH13.K, PH14.K, PH15.K, PH16.K
GND.1: M1.J1.4, M2.J1.4, M3.J1.4, M4.J1.4, M5.J1.4, M6.J1.4, M7.J1.4, M8.J1.4
unnamed: LED1.A, R1.1
unnamed: LED2.A, R2.1
unnamed: LED3.A, R3.1
unnamed: LED4.A, R4.1
unnamed: LED5.A, R5.1
unnamed: LED6.A, R6.1
unnamed: LED7.A, R7.1
unnamed: LED8.A, R8.1
unnamed: LED9.A, R9.1
unnamed: LED10.A, R10.1
unnamed: LED11.A, R11.1
unnamed: LED12.A, R12.1
unnamed: LED13.A, R13.1
unnamed: LED14.A, R14.1
unnamed: LED15.A, R15.1
unnamed: LED16.A, R16.1
unnamed: LED18.A, R20.1
unnamed: LED19.A, R21.1
unnamed: LED17.A, R17.2
unnamed: LED20.A, R22.1
unnamed: LED21.A, R23.1
unnamed: LED22.A, R24.1
unnamed: LED23.A, R25.1
unnamed: LED24.A, R26.1
unnamed: LED25.A, R27.1
unnamed: LED26.A, R28.1
unnamed: LED27.A, R29.1
unnamed: LED28.A, R30.1
unnamed: LED29.A, R31.1
unnamed: LED30.A, R32.1
unnamed: LED31.A, R33.1
unnamed: LED32.A, R34.1
unnamed: LED33.A, R35.1
unnamed: LED34.A, R36.2
unnamed: LED35.A, R39.1
unnamed: LED36.A, R40.1
unnamed: LED37.A, R41.1
unnamed: LED38.A, R42.1
unnamed: LED39.A, R43.1
unnamed: LED40.A, R44.1
unnamed: LED41.A, R45.1
unnamed: LED42.A, R46.1
unnamed: LED43.A, R47.1
unnamed: LED44.A, R48.1
unnamed: LED45.A, R49.1
unnamed: LED46.A, R50.1
unnamed: LED47.A, R51.1
unnamed: LED48.A, R52.1
unnamed: LED49.A, R53.1
unnamed: LED50.A, R54.1
unnamed: LED51.A, R55.2
unnamed: LED52.A, R58.1
unnamed: LED53.A, R59.1
unnamed: LED54.A, R60.1
unnamed: LED55.A, R61.1
unnamed: LED56.A, R62.1
unnamed: LED57.A, R63.1
unnamed: LED58.A, R64.1
unnamed: LED59.A, R65.1
unnamed: LED60.A, R66.1
unnamed: LED61.A, R67.1
unnamed: LED62.A, R68.1
unnamed: LED63.A, R69.1
unnamed: LED64.A, R70.1
unnamed: LED65.A, R71.1
unnamed: LED66.A, R72.1
unnamed: LED67.A, R73.1
unnamed: LED68.A, R74.2
unnamed: LED69.A, R77.1
unnamed: LED70.A, R78.1
unnamed: LED71.A, R79.1
unnamed: LED72.A, R80.1
unnamed: LED73.A, R81.1
unnamed: LED74.A, R82.1
unnamed: LED75.A, R83.1
unnamed: LED76.A, R84.1
unnamed: LED77.A, R85.1
unnamed: LED78.A, R86.1
unnamed: LED79.A, R87.1
unnamed: LED80.A, R88.1
unnamed: LED81.A, R89.1
unnamed: LED82.A, R90.1
unnamed: LED83.A, R91.1
unnamed: LED84.A, R92.1
unnamed: LED85.A, R93.2
unnamed: LED86.A, R96.1
unnamed: LED87.A, R97.1
unnamed: LED88.A, R98.1
unnamed: LED89.A, R99.1
unnamed: LED90.A, R100.1
unnamed: LED91.A, R101.1
unnamed: LED92.A, R102.1
unnamed: LED93.A, R103.1
unnamed: LED94.A, R104.1
unnamed: LED95.A, R105.1
unnamed: LED96.A, R106.1
unnamed: LED97.A, R107.1
unnamed: LED98.A, R108.1
unnamed: LED99.A, R109.1
unnamed: LED100.A, R110.1
unnamed: LED101.A, R111.1
unnamed: LED102.A, R112.2
unnamed: LED103.A, R115.1
unnamed: LED104.A, R116.1
unnamed: LED105.A, R117.1
unnamed: LED106.A, R118.1
unnamed: LED107.A, R119.1
unnamed: LED108.A, R120.1
unnamed: LED109.A, R121.1
unnamed: LED110.A, R122.1
unnamed: LED111.A, R123.1
unnamed: LED112.A, R124.1
unnamed: LED113.A, R125.1
unnamed: LED114.A, R126.1
unnamed: LED115.A, R127.1
unnamed: LED116.A, R128.1
unnamed: LED117.A, R129.1
unnamed: LED118.A, R130.1
unnamed: LED119.A, R131.2
unnamed: LED120.A, R134.1
unnamed: LED121.A, R135.1
unnamed: LED122.A, R136.1
unnamed: LED123.A, R137.1
unnamed: LED124.A, R138.1
unnamed: LED125.A, R139.1
unnamed: LED126.A, R140.1
unnamed: LED127.A, R141.1
unnamed: LED128.A, R142.1
unnamed: LED129.A, R143.1
unnamed: LED130.A, R144.1
unnamed: LED131.A, R145.1
unnamed: LED132.A, R146.1
unnamed: LED133.A, R147.1
unnamed: LED134.A, R148.1
unnamed: LED135.A, R149.1
unnamed: LED136.A, R150.2
VIN: M1.J2.1, M2.J2.1, M3.J2.1, M4.J2.1, M5.J2.1, M6.J2.1, M7.J2.1, M8.J2.1

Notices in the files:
parts and their libraries:
SparkFun-Connectors: Licensing: Creative Commons ShareAlike 4.0 International - https://creativecommons.org/licenses/by-sa/4.0
diy-modules: Released under the Creative Commons Attribution 4.0 International License: http://creativecommons.org/licenses/by/4.0
